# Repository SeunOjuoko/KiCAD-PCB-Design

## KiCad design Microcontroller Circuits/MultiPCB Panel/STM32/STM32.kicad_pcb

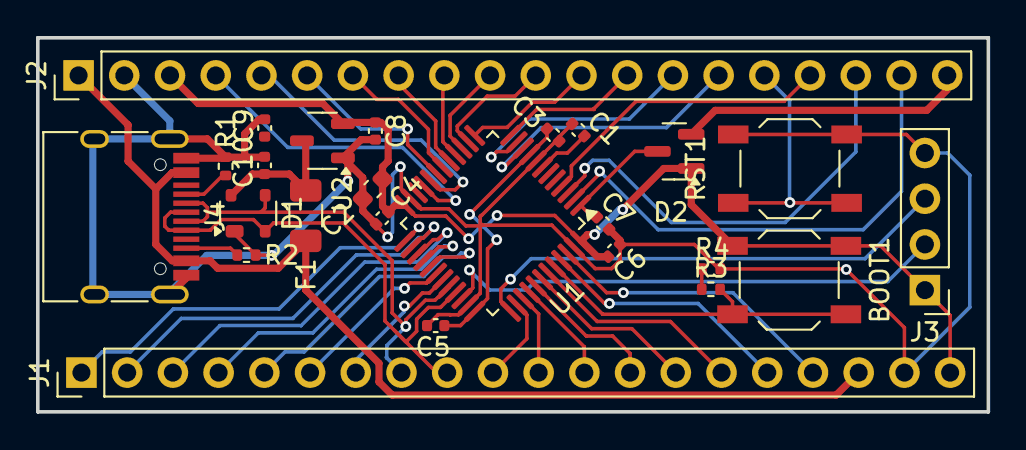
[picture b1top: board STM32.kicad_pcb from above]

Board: 2 copper layers, 52.8 x 20.8 mm, 25 parts (0 on the bottom side), 45 nets.

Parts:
BOOT1: SW_SPST; SW_SPST_TL3342
C1, C3, C4, C5, C6, C7, C10: 100nF; C_0402_1005Metric
C2: 10uF; C_0603_1608Metric
C8, C9: 1uF; C_0402_1005Metric
D1: PRTR5V0U2X; SOT-143
D2: BAT54C; SOT-23
F1: 500mA; Fuse_1206_3216Metric
J1, J2: Conn_01x20; PinHeader_1x20_P2.54mm_Vertical
J3: Conn_01x04; PinHeader_1x04_P2.54mm_Vertical
J4: USB_C_Receptacle_USB2.0_16P; USB_C_Receptacle_HRO_TYPE-C-31-M-12
R1, R2, R3, R4: 5K1; R_0402_1005Metric
RST1: SW_SPST; SW_SPST_TL3342
U1: STM32F072CBTx; LQFP-48_7x7mm_P0.5mm
U2: XC6206PxxxMR; SOT-23-3

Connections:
+3V3: BOOT1.1 (A), C2.1, C3.1, C4.1, C5.1, C6.1, C8.1, D2.1, J1.20, J2.3, J3.1, U1.9 (VDDA), U1.24 (VDD), U1.36 (VDDIO2), U1.48 (VDD), U2.2 (VO)
+5V: C9.1, C10.1, D1.4 (VCC), F1.2, U2.3 (VI)
+BATT: C7.1, D2.3, U1.1 (VBAT)
A0: J2.15, U1.10 (PA0)
A1: J2.14, U1.11 (PA1)
A2: J2.13, U1.12 (PA2)
A3: J2.12, U1.13 (PA3)
A4: J2.11, U1.14 (PA4)
A5: J2.10, U1.15 (PA5)
A6: J2.9, U1.16 (PA6)
A7: J2.8, U1.17 (PA7)
A8: J1.5, U1.29 (PA8)
A9: J1.6, U1.30 (PA9)
A10: J1.7, U1.31 (PA10)
A13: J3.2, U1.34 (PA13)
A14: J3.3, U1.37 (PA14)
A15: J1.10, U1.38 (PA15)
B0: J2.7, U1.18 (PB0)
B1: J2.6, U1.19 (PB1)
B2: J2.5, U1.20 (PB2)
B3: J1.11, U1.39 (PB3)
B4: J1.12, U1.40 (PB4)
B5: J1.13, U1.41 (PB5)
B6: J1.14, U1.42 (PB6)
B7: J1.15, U1.43 (PB7)
B8: J1.16, U1.45 (PB8)
B9: J1.17, U1.46 (PB9)
B10: J2.4, U1.21 (PB10)
B12: J1.1, U1.25 (PB12)
B13: J1.2, U1.26 (PB13)
B14: J1.3, U1.27 (PB14)
B15: J1.4, U1.28 (PB15)
BOOT0: BOOT1.2 (B), R3.1, U1.44 (BOOT0)
C13: J2.19, U1.2 (PC13)
C14: J2.18, U1.3 (PC14)
C15: J2.17, U1.4 (PC15)
D+: D1.2 (I/O1), J1.9, J4.A6 (D+), J4.B6 (D+), U1.33 (PA12)
D-: D1.3 (I/O2), J1.8, J4.A7 (D-), J4.B7 (D-), U1.32 (PA11)
GND: C1.2, C2.2, C3.2, C4.2, C5.2, C6.2, C7.2, C8.2, C9.2, C10.2, D1.1 (GND), J1.19, J2.2, J3.4, J4.A1 (GND), J4.A12 (GND), J4.B1 (GND), J4.B12 (GND), J4.S1 (SHIELD), R1.2, R2.2, R4.1, RST1.2 (B), U1.8 (VSSA), U1.23 (VSS), U1.35 (VSS), U1.47 (VSS), U2.1 (GND)
NRST: C1.1, J2.16, RST1.1 (A), U1.7 (NRST)
unnamed: D2.2, J2.20
unnamed: J4.A5 (CC1), R1.1
unnamed: J4.B5 (CC2), R2.1
unnamed: R3.2, R4.2
VBUS: F1.1, J1.18, J2.1, J4.A4 (VBUS), J4.A9 (VBUS), J4.B4 (VBUS), J4.B9 (VBUS)

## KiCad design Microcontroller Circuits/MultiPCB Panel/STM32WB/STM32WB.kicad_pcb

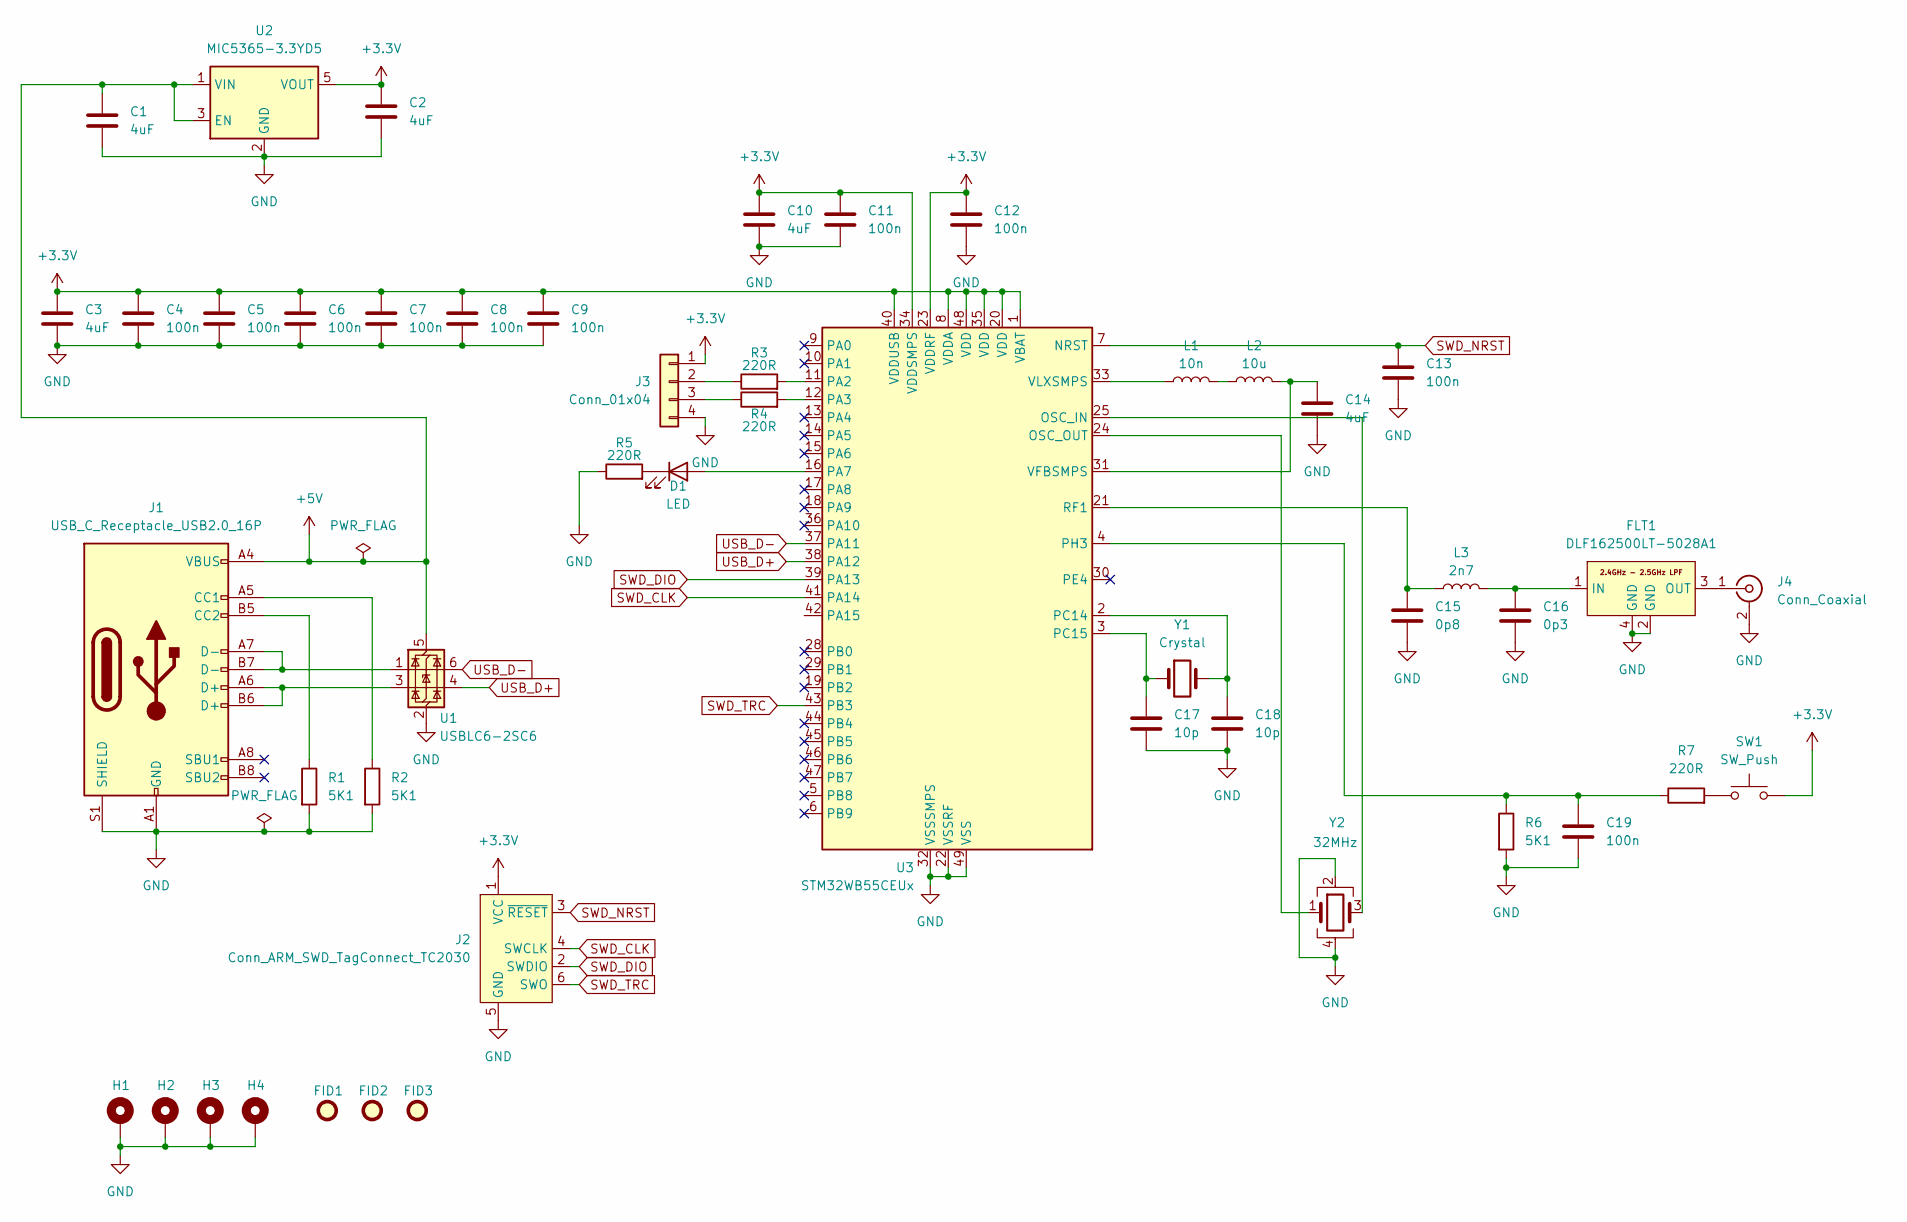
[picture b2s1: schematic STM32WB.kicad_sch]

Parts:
C1, C2, C3, C10, C14: 4uF; C_0603_1608Metric
C4, C5, C6, C7, C8, C9, C11, C12, C13, C19: 100n; C_0402_1005Metric
C15: 0p8; C_0603_1608Metric
C16: 0p3; C_0603_1608Metric
C17, C18: 10p; C_0402_1005Metric
D1: LED; LED_0402_1005Metric
FID1, FID2, FID3: Fiducial; Fiducial_0.5mm_Mask1.5mm
FLT1: DLF162500LT-5028A1; DLF162500LT5028A1
H1, H2, H3, H4: MountingHole_Pad; MountingHole_2.2mm_M2_Pad_Via
J1: USB_C_Receptacle_USB2.0_16P; USB_C_Receptacle_GCT_USB4105-xx-A_16P_TopMnt_Horizontal
J2: Conn_ARM_SWD_TagConnect_TC2030; Tag-Connect_TC2030-IDC-FP_2x03_P1.27mm_Vertical
J3: Conn_01x04; Molex_PicoBlade_53048-0410_1x04_P1.25mm_Horizontal
J4: Conn_Coaxial; U.FL_Hirose_U.FL-R-SMT-1_Vertical
L1: 10n; L_0402_1005Metric
L2: 10u; L_0805_2012Metric
L3: 2n7; L_0402_1005Metric
R1, R2, R6: 5K1; R_0402_1005Metric
R3, R4, R5, R7: 220R; R_0402_1005Metric
SW1: SW_Push; SW_SPST_CK_RS282G05A3
U1: USBLC6-2SC6; SOT-23-6
U2: MIC5365-3.3YD5; SOT-23-5
U3: STM32WB55CEUx; QFN-48-1EP_7x7mm_P0.5mm_EP5.6x5.6mm
Y1: Crystal; Crystal_SMD_2012-2Pin_2.0x1.2mm
Y2: 32MHz; Crystal_SMD_2016-4Pin_2.0x1.6mm

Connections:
+3.3V: C2.1, C3.1, C4.1, C5.1, C6.1, C7.1, C8.1, C9.1, C10.1, C11.1, C12.1, J2.1 (VCC), J3.1, SW1.2, U2.5 (VOUT), U3.1 (VBAT), U3.8 (VDDA), U3.20 (VDD), U3.23 (VDDRF), U3.34 (VDDSMPS), U3.35 (VDD), U3.40 (VDDUSB), U3.48 (VDD)
+5V: C1.1, J1.A4 (VBUS), J1.A9 (VBUS), J1.B4 (VBUS), J1.B9 (VBUS), U1.5 (VBUS), U2.1 (VIN), U2.3 (EN)
GND: C1.2, C2.2, C3.2, C4.2, C5.2, C6.2, C7.2, C8.2, C9.2, C10.2, C11.2, C12.2, C13.2, C14.2, C15.2, C16.2, C17.2, C18.2, C19.2, FLT1.2 (GND), FLT1.4 (GND), H1.1, H2.1, H3.1, H4.1, J1.A1 (GND), J1.A12 (GND), J1.B1 (GND), J1.B12 (GND), J1.S1 (SHIELD), J2.5 (GND), J3.4, J4.2 (Ext), R1.2, R2.2, R5.1, R6.2, U1.2 (GND), U2.2 (GND), U3.22 (VSSRF), U3.32 (VSSSMPS), U3.49 (VSS), Y2.2, Y2.4
unnamed: D1.2 (A), U3.16 (PA7)
unnamed: D1.1 (K), R5.2
unnamed: C16.1, FLT1.1 (IN), L3.2
unnamed: FLT1.3 (OUT), J4.1 (In)
unnamed: J1.A5 (CC1), R2.1
unnamed: J1.B5 (CC2), R1.1
unnamed: J1.A6 (D+), J1.B6 (D+), U1.3 (I/O2)
unnamed: J1.A7 (D-), J1.B7 (D-), U1.1 (I/O1)
unnamed: J3.2, R3.1
unnamed: J3.3, R4.1
unnamed: L1.2, L2.1
unnamed: R7.2, SW1.1
unnamed: U3.25 (OSC_IN), Y2.3
unnamed: U3.24 (OSC_OUT), Y2.1
unnamed: R3.2, U3.11 (PA2)
unnamed: R4.2, U3.12 (PA3)
unnamed: C18.1, U3.2 (PC14), Y1.2
unnamed: C17.1, U3.3 (PC15), Y1.1
unnamed: C19.1, R6.1, R7.1, U3.4 (PH3)
unnamed: C15.1, L3.1, U3.21 (RF1)
unnamed: C14.1, L2.2, U3.31 (VFBSMPS)
unnamed: L1.1, U3.33 (VLXSMPS)
SWD_CLK: J2.4 (SWCLK), U3.41 (PA14)
SWD_DIO: J2.2 (SWDIO), U3.39 (PA13)
SWD_NRST: C13.1, J2.3 (~RESET), U3.7 (NRST)
SWD_TRC: J2.6 (SWO), U3.43 (PB3)
USB_D+: U1.4 (I/O2), U3.38 (PA12)
USB_D-: U1.6 (I/O1), U3.37 (PA11)

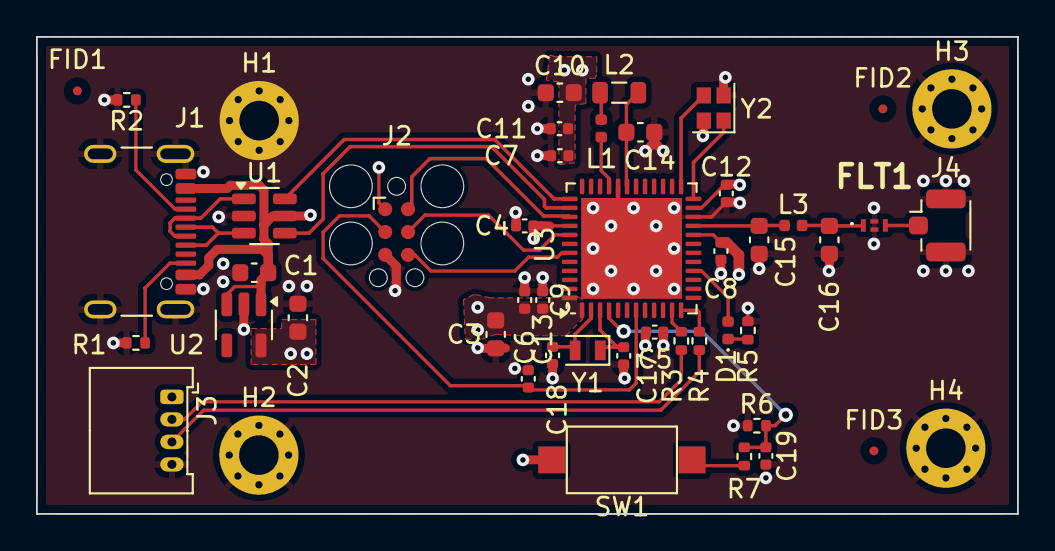
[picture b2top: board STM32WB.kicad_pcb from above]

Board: 4 copper layers, 54.5 x 26.5 mm, 48 parts (0 on the bottom side), 31 nets.
